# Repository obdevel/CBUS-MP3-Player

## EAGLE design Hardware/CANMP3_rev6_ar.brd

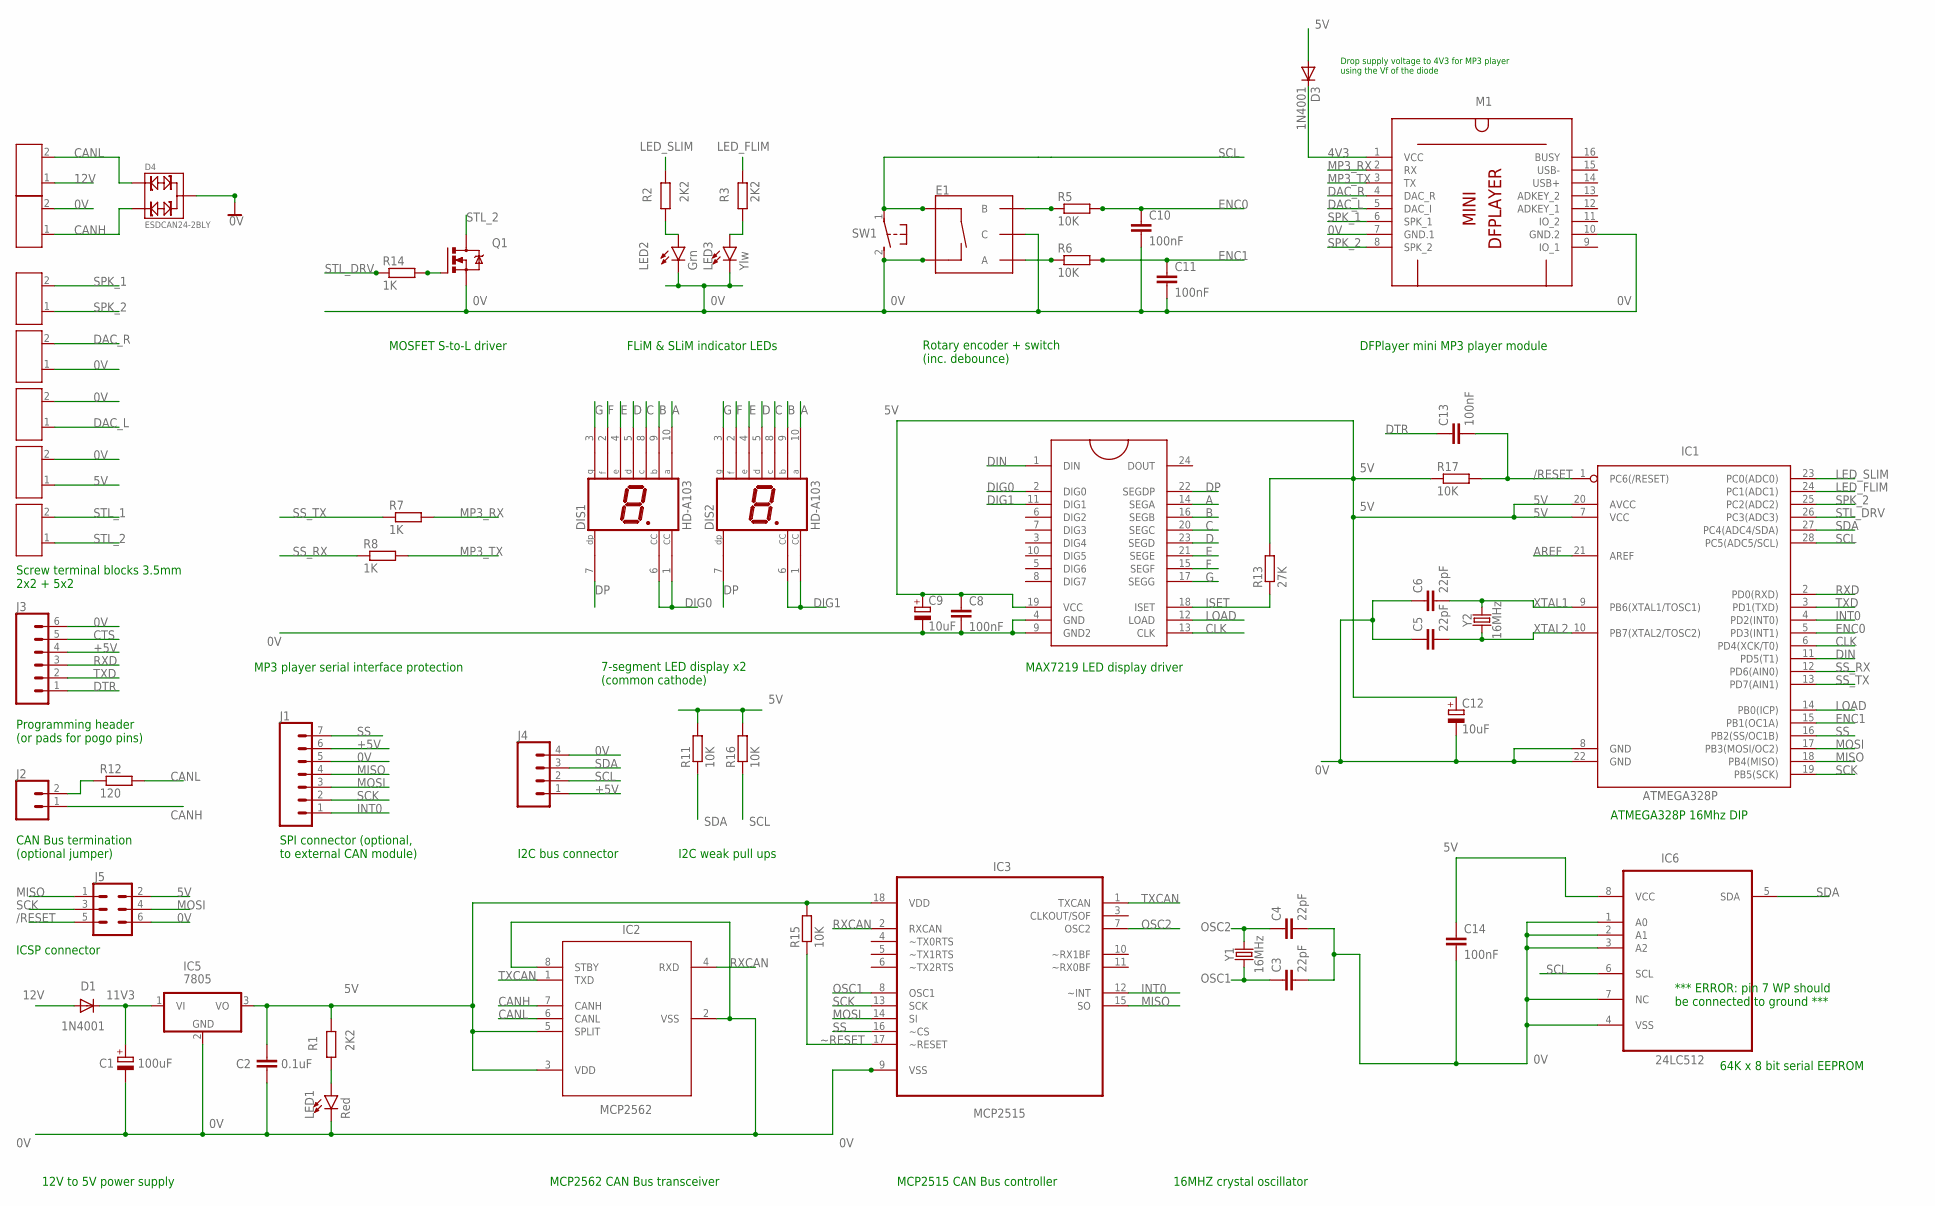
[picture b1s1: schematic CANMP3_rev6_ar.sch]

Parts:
C1: 100uF; E2,5-6
C2: 0.1uF; C025-025X050
C3, C4, C5, C6: 22pF; C025-024X044
C8, C10, C11, C13, C14: 100nF; C025-024X044
C9: 10uF; E2,5-5
C12: 10uF; E2,5-6E
D1, D3: 1N4001; DO41-10
D4: ESDCAN24-2BLY; SOT-23
DIS1, DIS2: HD-A103; HDSP-A
E1: ENCODER-SWITCH; ROTARY_ENC_PLAIN
IC1: ATMEGA328P; DIP28
IC2: MCP2562; PDIP8_300MC
IC3: MCP2515; DIP254P762X432-18
IC4: MAX7219; DIL24
IC5: 7805; TO220V
IC6: 24LC512; DIP254P762X432-8
J1: CONN_07; 1X07
J2: CONN_02; 1X02
J3: CONN_06SILK_FEMALE_PTH; 1X06
J4: CONN_04; 1X04
J5: FEMALE 2x3; 2X3
LED1: Red; LED_3MM
LED2: Grn; LED_3MM
LED3: Ylw; LED_3MM
M1: DFPLAYER-MINI-MODULE
Q1: IRF540; TO220BV
R1, R2, R3: 2K2; 0207/10
R5, R6, R11, R15, R16, R17: 10K; 0207/10
R7, R8, R14: 1K; 0207/10
R12: 120; 0207/10
R13: 27K; 0207/10
SW1: DTS-3
TB1, TB2, TB3, TB4, TB5, TB6, TB7: SCREW-TERMINAL-GREEN(2P-3.5); H2-3.5-7.0X7.0MM
Y1, Y2: 16MHz; HC49US

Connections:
0V: C1.-, C2.2, C3.2, C4.2, C5.1, C6.1, C8.2, C9.-, C10.2, C11.2, C12.-, C14.2, D4.3, E1.C, E1.SW-, IC1.8 (GND), IC1.22 (GND), IC2.2 (VSS), IC2.8 (STBY), IC3.9 (VSS), IC4.4 (GND), IC4.9 (GND2), IC5.2 (GND), IC6.1 (A0), IC6.2 (A1), IC6.3 (A2), IC6.4 (VSS), IC6.7 (NC), J1.5, J3.6, J4.4, J5.6, LED1.K (C), LED2.K (C), LED3.K (C), M1.7 (GND.1), M1.10 (GND.2), Q1.S, SW1.2, TB2.2, TB4.2, TB5.2, TB6.1
4V3: D3.C, M1.1 (VCC)
5V: C2.1, C8.1, C9.+, C12.+, C14.1, D3.A, IC1.7 (VCC), IC1.20 (AVCC), IC2.3 (VDD), IC2.5 (SPLIT), IC3.18 (VDD), IC4.19 (VCC), IC5.3 (VO), IC6.8 (VCC), J5.2, R1.2, R11.2, R13.2, R15.2, R16.2, R17.1, TB5.1
11V3: C1.+, D1.C, IC5.1 (VI)
12V: D1.A, TB1.1
+5V: J1.6, J3.4, J4.1
/RESET: C13.2, IC1.1 (PC6(/RESET)), J5.5, R17.2
A: DIS1.10 (A), DIS2.10 (A), IC4.14 (SEGA)
AREF: IC1.21 (AREF)
B: DIS1.9 (B), DIS2.9 (B), IC4.16 (SEGB)
C: DIS1.8 (C), DIS2.8 (C), IC4.20 (SEGC)
CANH: D4.2, IC2.7 (CANH), J2.1, TB2.1
CANL: D4.1, IC2.6 (CANL), R12.2, TB1.2
CLK: IC1.6 (PD4(XCK/T0)), IC4.13 (CLK)
CTS: J3.5
D: DIS1.5 (D), DIS2.5 (D), IC4.23 (SEGD)
DAC_L: M1.5 (DAC_I), TB4.1
DAC_R: M1.4 (DAC_R), TB6.2
DIG0: DIS1.1 (CC), DIS1.6 (CC), IC4.2 (DIG0)
DIG1: DIS2.1 (CC), DIS2.6 (CC), IC4.11 (DIG1)
DIN: IC1.11 (PD5(T1)), IC4.1 (DIN)
DP: DIS1.7 (DP), DIS2.7 (DP), IC4.22 (SEGDP)
DTR: C13.1, J3.1
E: DIS1.4 (E), DIS2.4 (E), IC4.21 (SEGE)
ENC0: C10.1, IC1.5 (PD3(INT1)), R5.2
ENC1: C11.1, IC1.15 (PB1(OC1A)), R6.2
F: DIS1.2 (F), DIS2.2 (F), IC4.15 (SEGF)
G: DIS1.3 (G), DIS2.3 (G), IC4.17 (SEGG)
INT0: IC1.4 (PD2(INT0)), IC3.12 (~INT), J1.1
ISET: IC4.18 (ISET), R13.1
LED_FLIM: IC1.24 (PC1(ADC1)), R3.2
LED_SLIM: IC1.23 (PC0(ADC0)), R2.2
LOAD: IC1.14 (PB0(ICP)), IC4.12 (LOAD)
MISO: IC1.18 (PB4(MISO)), IC3.15 (SO), J1.4, J5.1
MOSI: IC1.17 (PB3(MOSI/OC2)), IC3.14 (SI), J1.3, J5.4
MP3_RX: M1.2 (RX), R7.2
MP3_TX: M1.3 (TX), R8.2
unnamed: LED1.A, R1.1
unnamed: J2.2, R12.1
unnamed: E1.B, R5.1
unnamed: E1.A, R6.1
unnamed: LED2.A, R2.1
unnamed: LED3.A, R3.1
unnamed: Q1.G, R14.2
OSC1: C3.1, IC3.8 (OSC1), Y1.1
OSC2: C4.1, IC3.7 (OSC2), Y1.2
RXCAN: IC2.4 (RXD), IC3.2 (RXCAN)
RXD: IC1.2 (PD0(RXD)), J3.3
SCK: IC1.19 (PB5(SCK)), IC3.13 (SCK), J1.2, J5.3
SCL: E1.SW+, IC1.28 (PC5(ADC5/SCL)), IC6.6 (SCL), J4.2, R16.1, SW1.1
SDA: IC1.27 (PC4(ADC4/SDA)), IC6.5 (SDA), J4.3, R11.1
SPK_1: M1.6 (SPK_1), TB3.2
SPK_2: IC1.25 (PC2(ADC2)), M1.8 (SPK_2), TB3.1
SS: IC1.16 (PB2(SS/OC1B)), IC3.16 (~CS), J1.7
SS_RX: IC1.12 (PD6(AIN0)), R8.1
SS_TX: IC1.13 (PD7(AIN1)), R7.1
STL_1: TB7.2
STL_2: Q1.D, TB7.1
STL_DRV: IC1.26 (PC3(ADC3)), R14.1
TXCAN: IC2.1 (TXD), IC3.1 (TXCAN)
TXD: IC1.3 (PD1(TXD)), J3.2
XTAL1: C6.2, IC1.9 (PB6(XTAL1/TOSC1)), Y2.2
XTAL2: C5.2, IC1.10 (PB7(XTAL2/TOSC2)), Y2.1
~RESET: IC3.17 (~RESET), R15.1

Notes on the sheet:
MAX7219 LED display driver
MCP2562 CAN Bus transceiver
12V to 5V power supply
MCP2515 CAN Bus controller
MOSFET S-to-L driver
DFPlayer mini MP3 player module
Rotary encoder + switch (inc. debounce)
MP3 player serial interface protection
Screw terminal blocks 3.5mm 2x2 + 5x2
CAN Bus termination (optional jumper)
FLiM & SLiM indicator LEDs
7-segment LED display x2 (common cathode)
16MHZ crystal oscillator
SPI connector (optional, to external CAN module)
Programming header (or pads for pogo pins)
ATMEGA328P 16Mhz DIP
Drop supply voltage to 4V3 for MP3 player using the Vf of the diode
64K x 8 bit serial EEPROM
I2C bus connector
ICSP connector
*** ERROR: pin 7 WP should be connected to ground ***
I2C weak pull ups

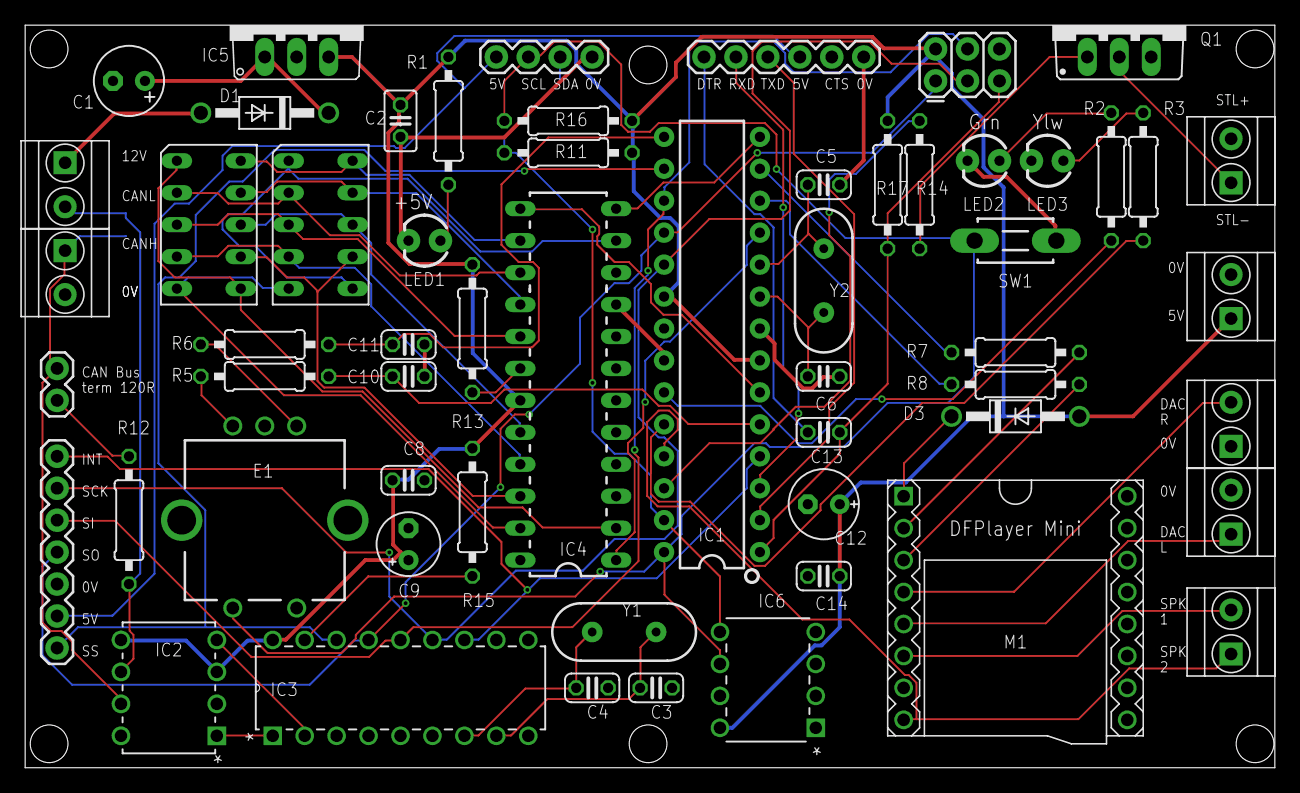
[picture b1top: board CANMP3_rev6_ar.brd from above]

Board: 2 copper layers, 99.4 x 59.0 mm, 59 parts (1 on the bottom side), 61 nets.

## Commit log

2018-06-25 Initial codebase commit
    Initial upload and commit of existing codebase
2018-06-25 Add hardware files
    Eagle files, Gerbers and docs

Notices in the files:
Hardware/CANMP3_rev6_ar.brd:
© Duncan Greenwood January 2018
parts and their libraries:
SparkFun-LED: Licensing: Creative Commons ShareAlike 4.0 International - https://creativecommons.org/licenses/by-sa/4.0
diy-modules: Released under the Creative Commons Attribution 4.0 International License: http://creativecommons.org/licenses/by/4.0
